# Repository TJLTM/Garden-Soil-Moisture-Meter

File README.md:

# Garden-Soil-Moisture-Meter
esp8266 based soil moisture meter. 

Stupid simple. this is a resistive soil meter. based on teh esp8266 minimal components and code. Uses MQTT. 

18650 Battery 
ESP8266 
3.5 inch stainless steel nails or screws x2

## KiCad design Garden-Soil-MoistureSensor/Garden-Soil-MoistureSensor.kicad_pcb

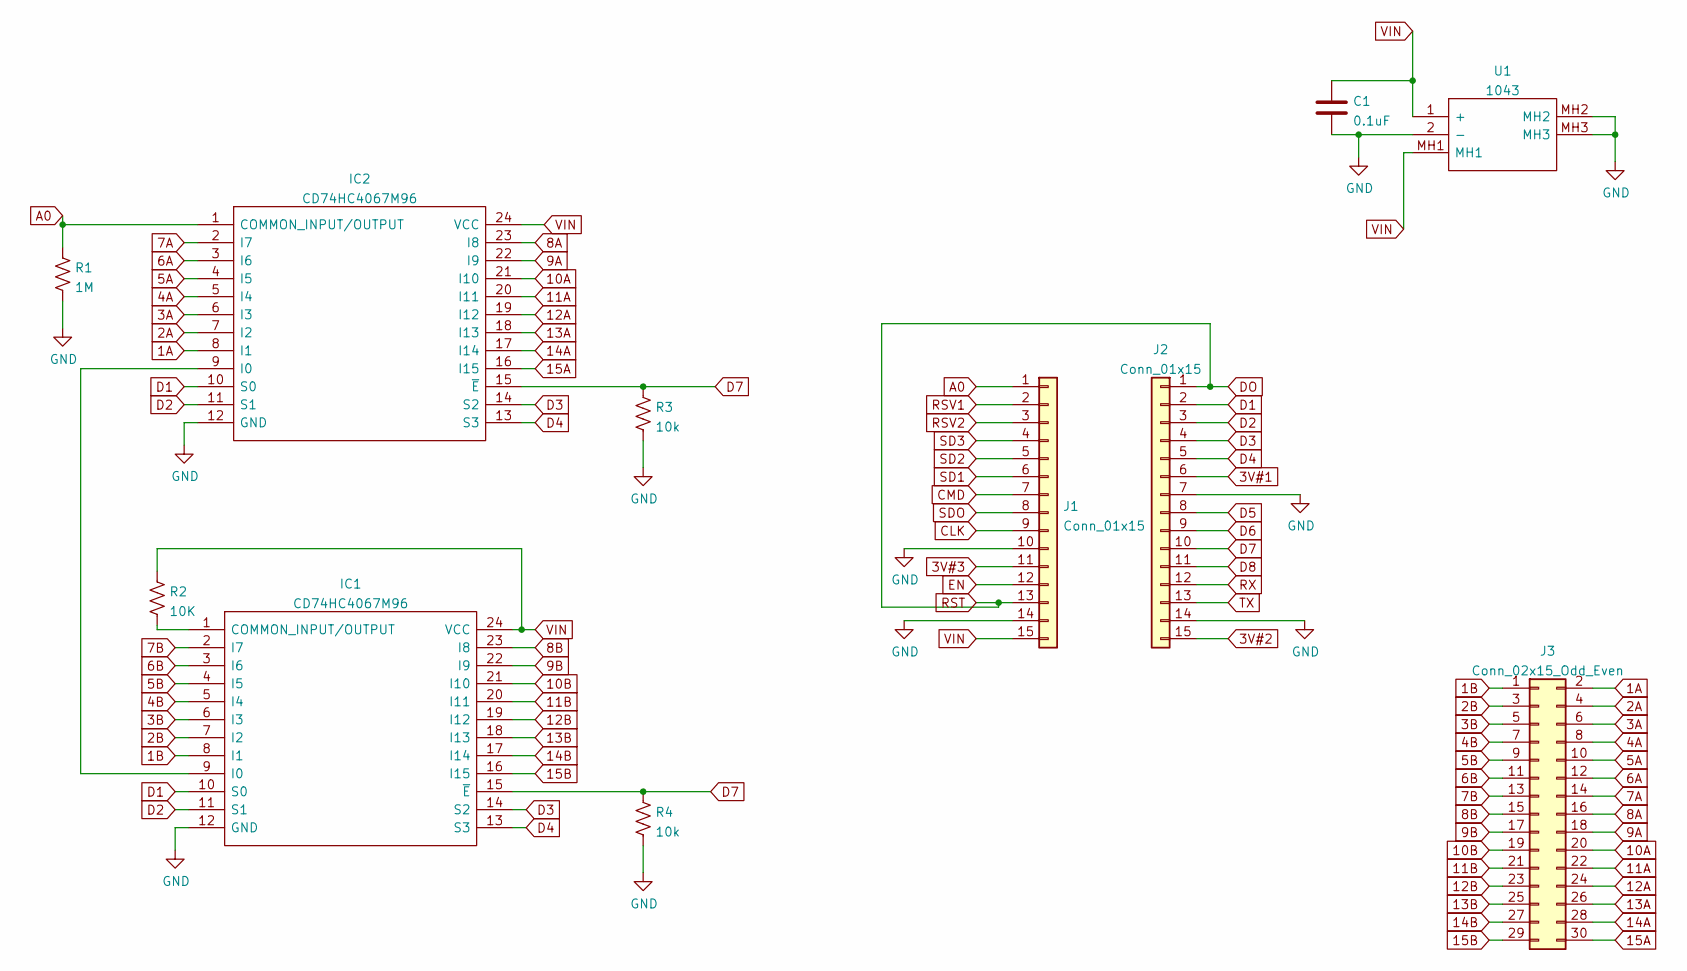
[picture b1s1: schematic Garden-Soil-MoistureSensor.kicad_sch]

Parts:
C1: 0.1uF; C_Disc_D6.0mm_W2.5mm_P5.00mm
IC1, IC2: CD74HC4067M96; SOIC127P1030X265-24N; Mouser Part Number 595-CD74HC4067M96
J1, J2: Conn_01x15; PinHeader_1x15_P2.54mm_Vertical
J3: Conn_02x15_Odd_Even; PinSocket_2x15_P2.54mm_Horizontal
R1: 1M; R_Axial_DIN0207_L6.3mm_D2.5mm_P2.54mm_Vertical
R2: 10K; R_Axial_DIN0207_L6.3mm_D2.5mm_P2.54mm_Vertical
R3, R4: 10k; R_Axial_DIN0207_L6.3mm_D2.5mm_P2.54mm_Vertical
U1: 1043; Mouser Part Number 534-1043

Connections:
1A: IC2.8 (I1), J3.2
1B: IC1.8 (I1), J3.1
2A: IC2.7 (I2), J3.4
2B: IC1.7 (I2), J3.3
3A: IC2.6 (I3), J3.6
3B: IC1.6 (I3), J3.5
3V#1: J2.6
3V#2: J2.15
3V#3: J1.11
4A: IC2.5 (I4), J3.8
4B: IC1.5 (I4), J3.7
5A: IC2.4 (I5), J3.10
5B: IC1.4 (I5), J3.9
6A: IC2.3 (I6), J3.12
6B: IC1.3 (I6), J3.11
7A: IC2.2 (I7), J3.14
7B: IC1.2 (I7), J3.13
8A: IC2.23 (I8), J3.16
8B: IC1.23 (I8), J3.15
9A: IC2.22 (I9), J3.18
9B: IC1.22 (I9), J3.17
10A: IC2.21 (I10), J3.20
10B: IC1.21 (I10), J3.19
11A: IC2.20 (I11), J3.22
11B: IC1.20 (I11), J3.21
12A: IC2.19 (I12), J3.24
12B: IC1.19 (I12), J3.23
13A: IC2.18 (I13), J3.26
13B: IC1.18 (I13), J3.25
14A: IC2.17 (I14), J3.28
14B: IC1.17 (I14), J3.27
15A: IC2.16 (I15), J3.30
15B: IC1.16 (I15), J3.29
A0: IC2.1 (COMMON_INPUT/OUTPUT), J1.1, R1.1
CLK: J1.9
CMD: J1.7
D1: IC1.10 (S0), IC2.10 (S0), J2.2
D2: IC1.11 (S1), IC2.11 (S1), J2.3
D3: IC1.14 (S2), IC2.14 (S2), J2.4
D4: IC1.13 (S3), IC2.13 (S3), J2.5
D5: J2.8
D6: J2.9
D7: IC1.15 (~E), IC2.15 (~E), J2.10, R3.1, R4.1
D8: J2.11
DO: J1.13, J2.1
EN: J1.12
unnamed: IC1.1 (COMMON_INPUT/OUTPUT), R2.2
unnamed: IC1.9 (I0), IC2.9 (I0)
RSV1: J1.2
RSV2: J1.3
RX: J2.12
SD1: J1.6
SD2: J1.5
SD3: J1.4
SDO: J1.8
TX: J2.13
VIN: C1.1, IC1.24 (VCC), IC2.24 (VCC), J1.15, R2.1, U1.1 (+), U1.MH1

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
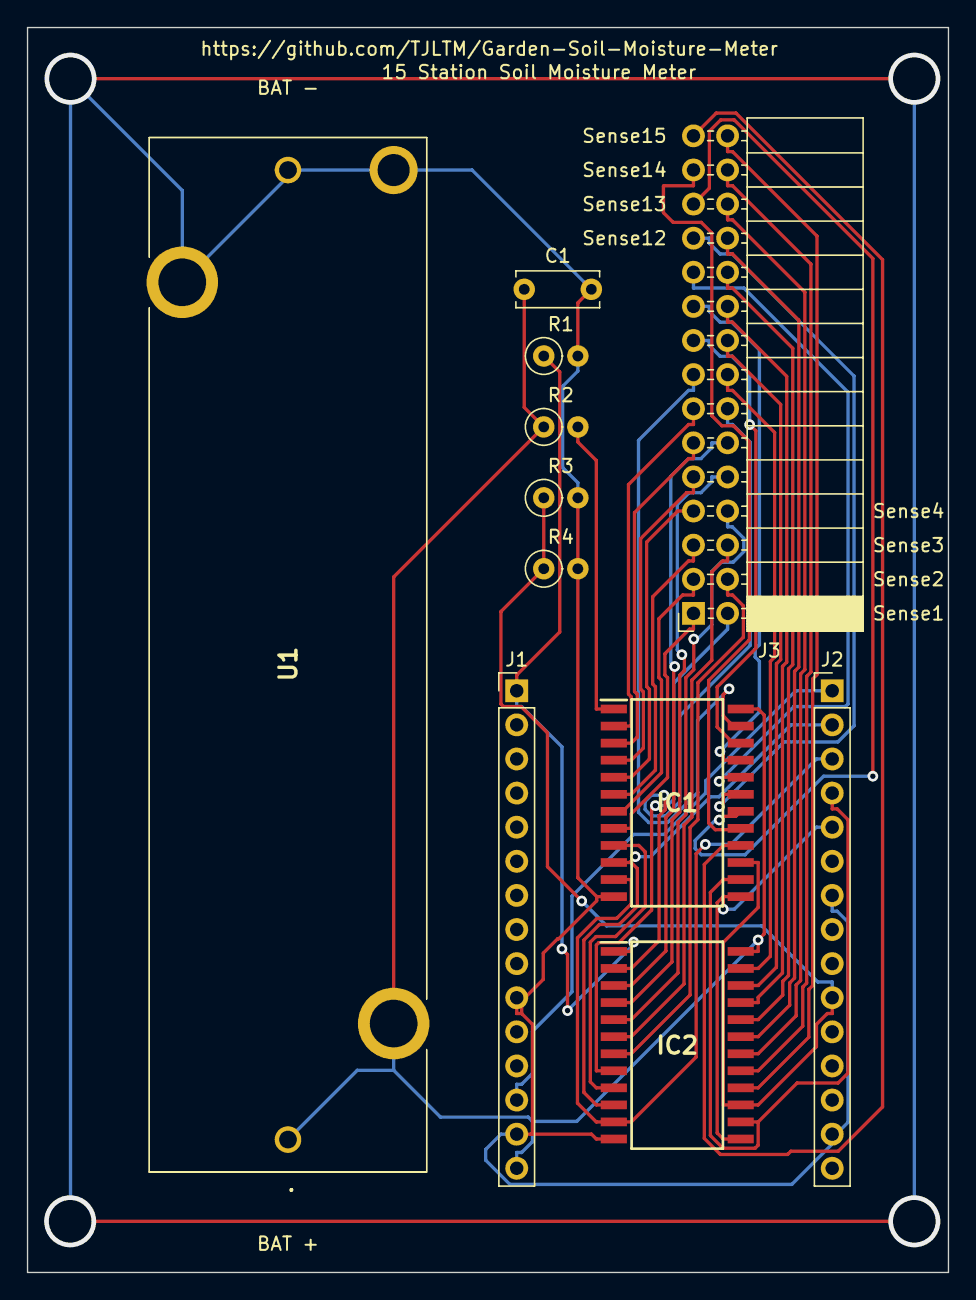
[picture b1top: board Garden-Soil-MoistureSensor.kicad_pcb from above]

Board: 2 copper layers, 68.6 x 92.7 mm, 11 parts (0 on the bottom side), 41 nets.

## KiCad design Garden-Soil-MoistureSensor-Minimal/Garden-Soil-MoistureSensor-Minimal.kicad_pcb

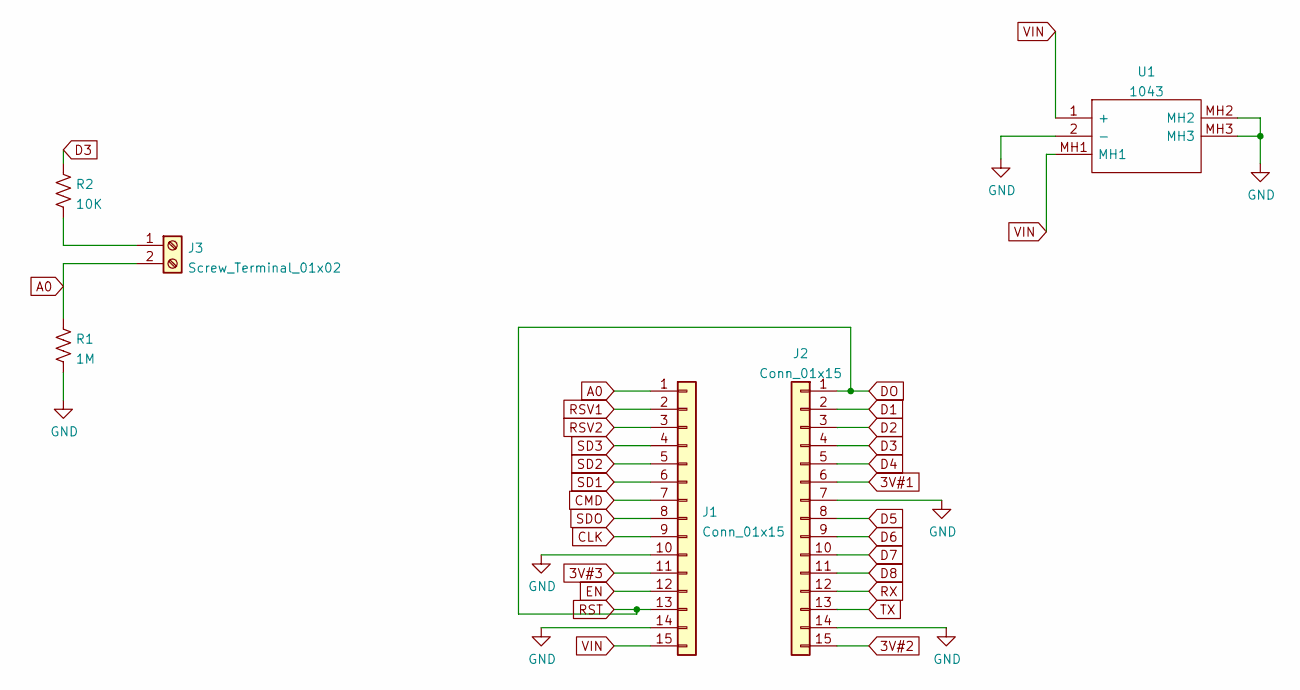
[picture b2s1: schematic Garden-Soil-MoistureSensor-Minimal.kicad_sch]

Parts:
J1, J2: Conn_01x15; PinHeader_1x15_P2.54mm_Vertical
J3: Screw_Terminal_01x02; TerminalBlock_Phoenix_MKDS-1,5-2-5.08_1x02_P5.08mm_Horizont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
R1: 1M; R_Axial_DIN0207_L6.3mm_D2.5mm_P2.54mm_Vertical
R2: 10K; R_Axial_DIN0207_L6.3mm_D2.5mm_P2.54mm_Vertical
U1: 1043; Mouser Part Number 534-1043

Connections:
3V#1: J2.6
3V#2: J2.15
3V#3: J1.11
A0: J1.1, J3.2, R1.1
CLK: J1.9
CMD: J1.7
D1: J2.2
D2: J2.3
D3: J2.4, R2.1
D4: J2.5
D5: J2.8
D6: J2.9
D7: J2.10
D8: J2.11
DO: J1.13, J2.1
EN: J1.12
GND: J1.10, J1.14, J2.7, J2.14, R1.2, U1.2 (-), U1.MH2, U1.MH3
unnamed: J3.1, R2.2
RSV1: J1.2
RSV2: J1.3
RX: J2.12
SD1: J1.6
SD2: J1.5
SD3: J1.4
SDO: J1.8
TX: J2.13
VIN: J1.15, U1.1 (+), U1.MH1

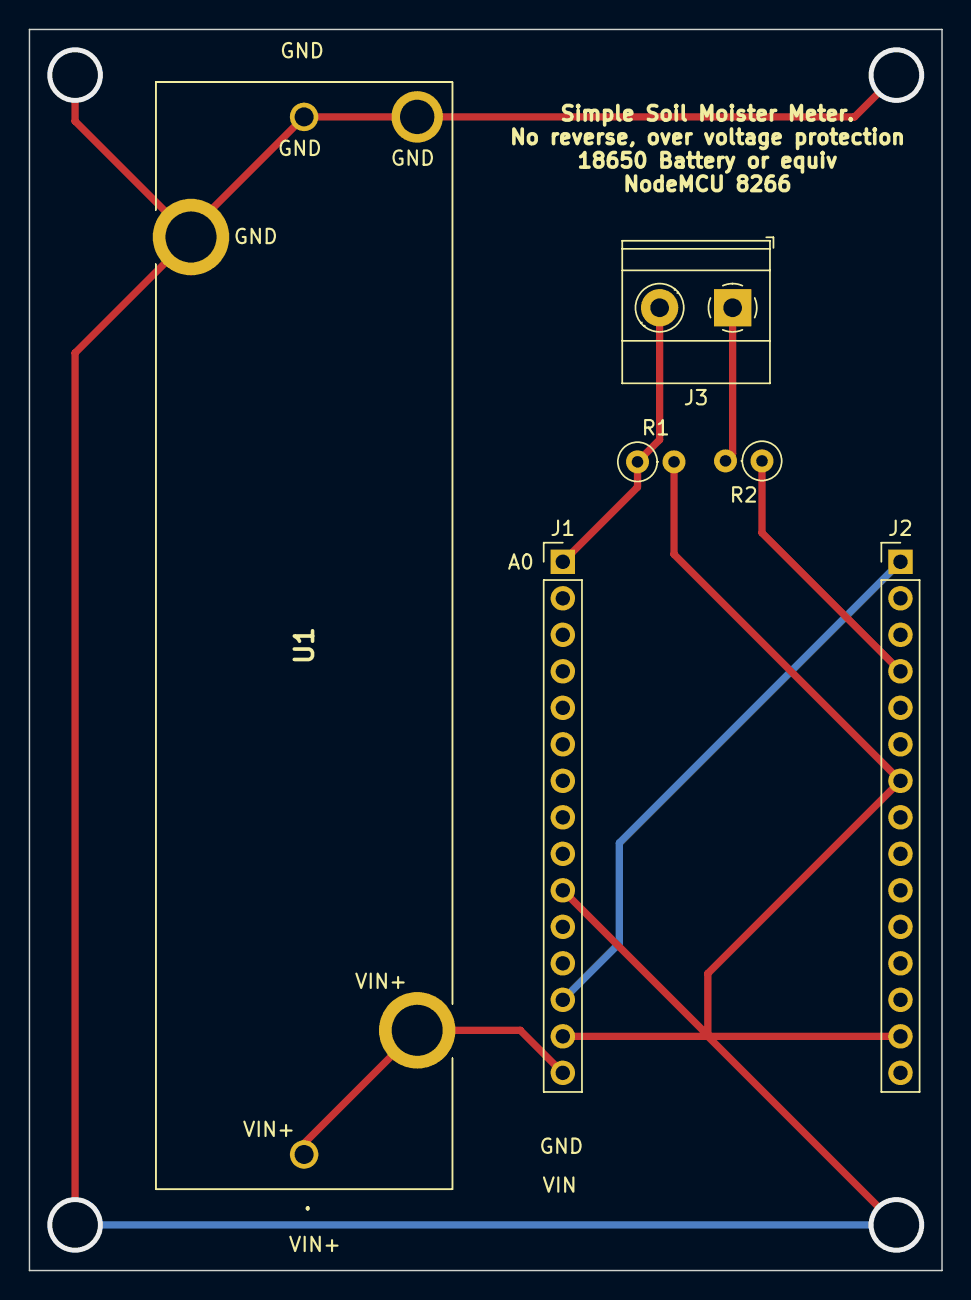
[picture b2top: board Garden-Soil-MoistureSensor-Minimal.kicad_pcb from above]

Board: 2 copper layers, 63.5 x 86.4 mm, 6 parts (0 on the bottom side), 6 nets.

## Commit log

2022-04-08 initial. Need to get a few other parts before i put docs, schematics or anything else.
2022-04-10 removing battery read as the 8266 only have one ADC
2022-04-12 currently working looks calibrated. needs to be built and deployed.
2022-04-12 putting in an easy way to set the sleep time.
2022-04-12 putting the Serial statements back in.
2022-04-12 Create LICENSE
2022-04-13 adding solidworks part file for DIY sensor. adding kicad project for the board.
2022-04-14 updated 3d part for testing.
2022-04-15 working on the PCB still selecting/designing things.
2022-04-15 adding a PCB mount 18650 battery holder.
2022-04-17 fixing the spacing for the sensor. using a store bought moisture sensor and attempting to calibrate this shows that the rods are too close to one another.
2022-04-19 working on a way to check the battery voltage.
2022-04-19 adding a PCBmount 18650 battery holder. still a wip
2022-04-19 board redesign adding some Muxes to be able to measure multiple sensors and (GASP) battery voltage. adding in logic for wifi unable to be connected to and exit. removing some MQTT stuff that i don't 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
2022-04-19 wip on adding the MUXes.
2022-04-20 autoformat working on MQTT and Wifi connection handling with timeouts. changed sleep duration if can't connect to wifi.
2022-04-20 got the basics into the schematic. I may rename this model "Liquid Squid" or something like that.
2022-04-20 doing some routing and footprint assignments.
2022-04-22 adding a minimal single sensor design and code.
2022-04-22 removing back up zips from kicad
2022-04-22 missed one
2022-04-22 forgot to add the D3 pin as the way to power the sensor.
2022-04-22 simple meter made DRCed and fab files put in. This seems like a waste to have fabbed for a single area but since i made the schematic people can make this on a bread board faster and cheaper then hav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
2022-04-22 changing the name from simple to minimal to match everything else. me no read.
2022-04-22 post fab change in kicad to remember where the fab files are.
2022-04-22 basic placement pre route
2022-04-22 drc fixes pre route
2022-04-22 post route needs to have silkscreen labels applied.
2022-04-22 finished bigger meter fab files ready.
2022-04-22 forgot it saves the fab file output after it outputs the files...
